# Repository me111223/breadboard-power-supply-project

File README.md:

# breadboard-power-supply-project
This project is a compact and reliable power supply module designed to plug directly into a standard breadboard (MB102). It provides stable DC voltage for electronic prototyping and hobbyist projects.

Key Features:

- Breadboard Compatible: Specifically designed to fit standard breadboard power rails.

- Dual Voltage Support: [Write your output voltages, e.g., Switchable 3.3V / 5V output].

- Input Connector: DC Barrel Jack (2.1mm) for external power adapters.

- Status Indicator: Integrated Power LED to show the current operating state.

Hardware Overview:

- The design focuses on simplicity and efficiency using the following key components:

- Voltage Regulators: [e.g., AMS1117 Series]

- Capacitors: Electrolytic and Ceramic for stable ripple filtering.

- Switching: [Mention any jumpers or slide switches used for voltage selection].

Project Structure: 

- /breadboard power supply.kicad_sch: Schematic design files.

- /breadboard power supply.kicad_pcb: PCB layout files.

- /breadboardpower supplyPCB-gerber: Production-ready Gerber files for manufacturing.

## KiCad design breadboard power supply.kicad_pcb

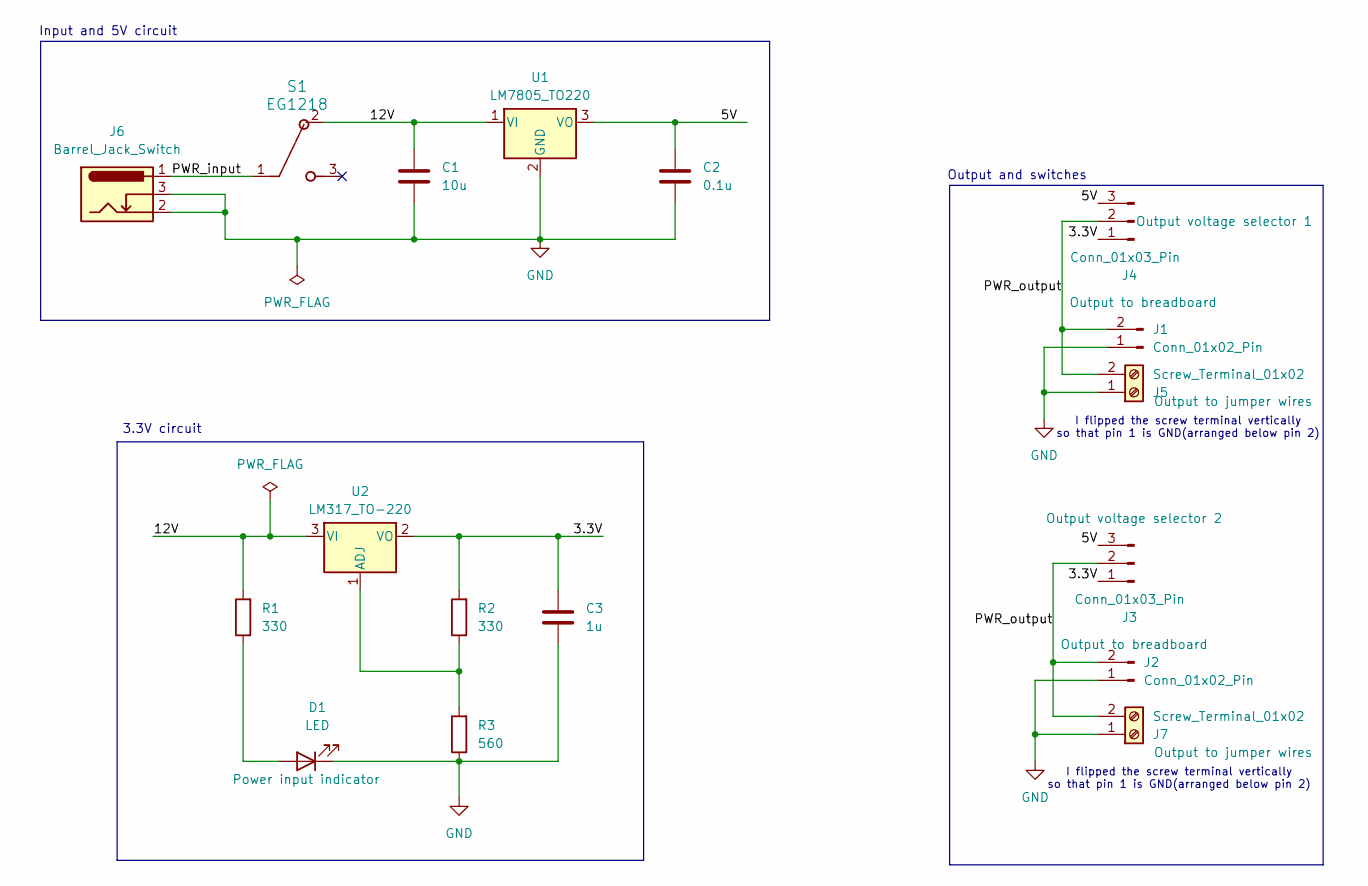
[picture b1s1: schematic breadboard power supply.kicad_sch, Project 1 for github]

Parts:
C1: 10u; C_Disc_D3.0mm_W1.6mm_P2.50mm
C2: 0.1u; C_Disc_D3.0mm_W1.6mm_P2.50mm
C3: 1u; C_Disc_D3.0mm_W1.6mm_P2.50mm
D1: LED; LED_D5.0mm
J1, J2: Conn_01x02_Pin; PinHeader_1x02_P2.54mm_Vertical
J3, J4: Conn_01x03_Pin; PinHeader_1x03_P2.54mm_Vertical
J5, J7: Screw_Terminal_01x02; TerminalBlock_CUI_TB007-508-02_1x02_P5.08mm_Horizontal
J6: Barrel_Jack_Switch; BarrelJack_Horizontal
R1, R2: 330; R_Axial_DIN0204_L3.6mm_D1.6mm_P7.62mm_Horizontal
R3: 560; R_Axial_DIN0204_L3.6mm_D1.6mm_P7.62mm_Horizontal
S1: EG1218; SW_1218_EWI
U1: LM7805_TO220; TO-220-3_Vertical
U2: LM317_TO-220; TO-220-3_Vertical

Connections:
/3.3V: C3.2, J3.1, J4.1, R2.2, U2.2 (VO)
/5V: C2.1, J3.3, J4.3, U1.3 (VO)
/12V: C1.1, R1.2, S1.2, U1.1 (VI), U2.3 (VI)
/PWR_input: J6.1, S1.1
/PWR_output: J1.2, J2.2, J3.2, J4.2, J5.2, J7.2
GND: C1.2, C2.2, C3.1, D1.1 (K), J1.1, J2.1, J5.1, J6.2, J6.3, J7.1, R3.1, U1.2 (GND)
unnamed: D1.2 (A), R1.1
unnamed: R2.1, R3.2, U2.1 (ADJ)

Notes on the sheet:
Output and switches
3.3V circuit
I flipped the screw terminal vertically so that pin 1 is GND(arranged below pin 2)
Input and 5V circuit

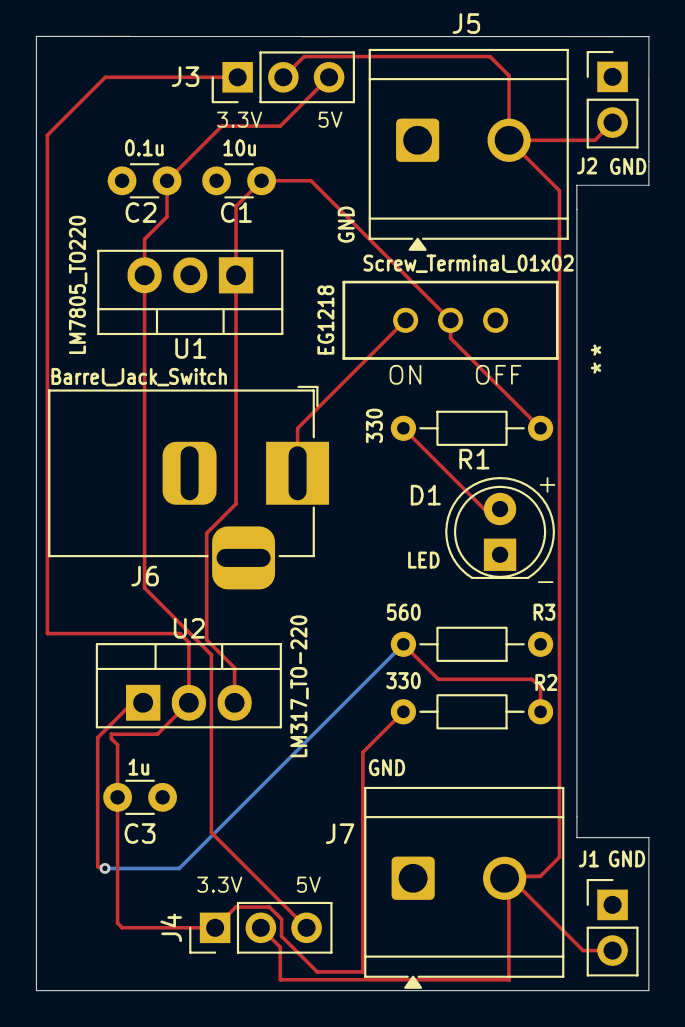
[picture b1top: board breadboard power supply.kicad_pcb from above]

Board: 2 copper layers, 34.0 x 53.0 mm, 17 parts (0 on the bottom side), 8 nets.

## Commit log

2026-02-22 Create images
